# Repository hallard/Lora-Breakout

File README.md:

RFM92 RFM95 RFM96 RFM98 Lora breakout board NRF24L01 socket
===========================================================

This is a utility breakout board for connecting Lora device onto 
NRF24L01 sockets

this breakout add also some other nice feature : 
- **Added** ATSHA204 for Crypto Authentication.
- **added** a Led to see what's going on.

Breakout comes in two versions, one with classic 2x4 PTH connector and the other with the same
but SMD version of the connector, this permit to have the PCB quite the same size of the original
RFM modules size. Oh, also these boards are rounded instead of corners.

This has been created to work with [ULPNode][7] Project and [ArduiPi][4] Project, but this breakout
can be used anywhere where you use NRF24L01 or has NRF24L01 connector.

The same breakout board exists also for RFM69W and RFM69HW on this [repo][2] and for RFM12B on this [one][1].
 
Check out news and other on my [blog][5], Any comments or question are welcomed on the [community][8]!

Detailed Description
====================

Everything will be soon documented on this dedicated [post][6].

## PTH connector version

### Schematic  

### Boards  
&nbsp;
&nbsp;

You can direct order PCB from this [link][10] to OSHPark.

## SMD connector version

### Schematic  

### Boards  
&nbsp;
&nbsp;

You can direct order PCB from this [link][11] to OSHPark.

Check out news and other on my [blog][5], Any comments or question are welcomed on the [community][8]!

[1]: https://github.com/hallard/RFM12B-BreakOut
[2]: https://github.com/hallard/RFM69W-BreakOut
[3]: http://hallard.me/rfm12b-breakout/ 
[4]: http://hallard.me/arduipi
[5]: http://hallard.me
[6]: http://hallard.me/lora-breakout/ 
[7]: http://hallard.me/category/ulpnode/
[8]: https://community.hallard.me/
[10]: https://oshpark.com/projects/XCiquSkv/order
[11]: https://oshpark.com/projects/V7WQxHGe/order

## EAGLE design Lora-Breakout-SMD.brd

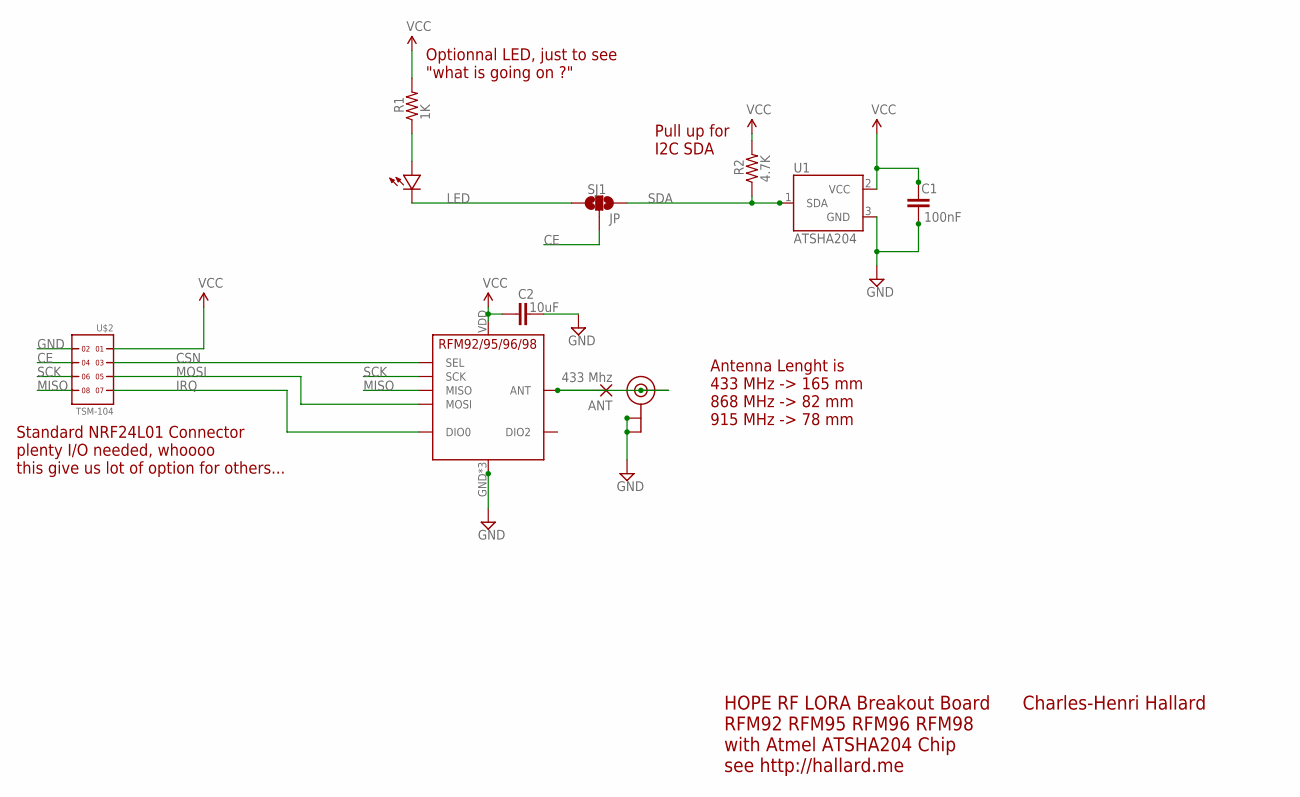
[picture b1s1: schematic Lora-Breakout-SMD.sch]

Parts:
ANT: 433 Mhz; 1,6/0,8
C1: 100nF; 0805-CAP
C2: 10uF; 0805-CAP
R1: 1K; 0805-RES
R2: 4.7K; 0805-RES
SJ1: JP; PAD-JUMPER-3-NO_YES_SILK
U1: ATSHA204; SOT23-3
U$1: LED0805-LARGE; 0805-LED-LARGEPADS
U$2: TSM-104
U$3: RFM95
U-FL: U.FL

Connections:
CE: SJ1.2, U$2.4
CSN: U$2.3, U$3.NSS (SEL)
GND: C1.2, C2.2, U1.3 (GND), U$2.2, U$3.GND, U$3.GND1 (GND), U$3.GND2 (GND), U-FL.1 (GND), U-FL.2 (GND)
IRQ: U$2.7, U$3.DIO0
LED: SJ1.1, U$1.MINUS
MISO: U$2.8, U$3.MISO
MOSI: U$2.5, U$3.MOSI
unnamed: ANT.1, U$3.ANT, U-FL.3 (SIGNAL)
unnamed: R1.1, U$1.PLUS
SCK: U$2.6, U$3.SCK
SDA: R2.1, SJ1.3, U1.1 (SDA)
VCC: C1.1, C2.1, R1.2, R2.2, U1.2 (VCC), U$2.1, U$3.VDD (VCC)

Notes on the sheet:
HOPE RF LORA Breakout Board RFM92 RFM95 RFM96 RFM98 with Atmel ATSHA204 Chip see http://hallard.me
Charles-Henri Hallard
Antenna Lenght is 433 MHz -> 165 mm 868 MHz -> 82 mm 915 MHz -> 78 mm
Optionnal LED, just to see "what is going on ?"
Standard NRF24L01 Connector plenty I/O needed, whoooo this give us lot of option for others...
Pull up for I2C SDA

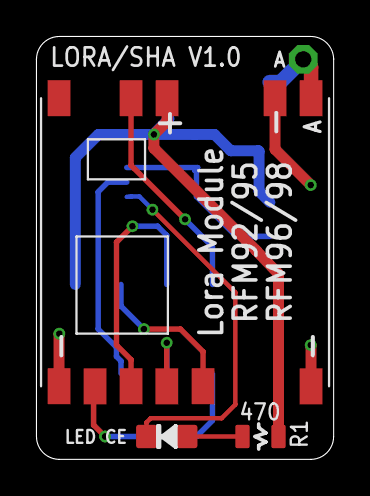
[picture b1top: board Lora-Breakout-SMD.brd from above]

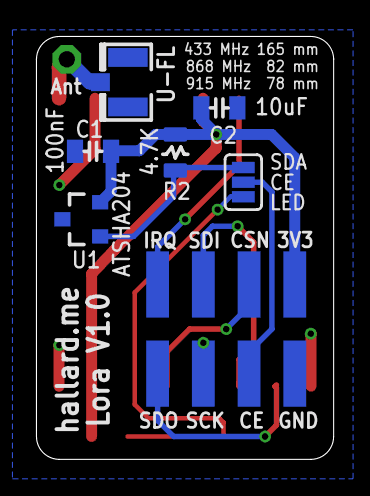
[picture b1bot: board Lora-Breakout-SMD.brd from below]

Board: 2 copper layers, 16.5 x 23.5 mm, 11 parts (7 on the bottom side), 12 nets.

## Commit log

2015-10-29 :neckbeard: Added .gitattributes & .gitignore files
2015-10-29 Creation
2015-10-29 Added OSHPark links
2015-10-29 Image resized
2015-10-29 Added ATSH204
2015-10-29 Cosmetic changes

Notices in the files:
parts and their libraries:
SparkFun-DigitalIC: Licensing: Creative Commons ShareAlike 4.0 International - https://creativecommons.org/licenses/by-sa/4.0
microbuilder: This work is placed in the public domain, and may be freely used for commercial and non-commercial work with the following conditions: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
